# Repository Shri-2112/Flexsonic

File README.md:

# FlexSonic – Smart Glove for Gesture-to-Speech Communication
A wearable assistive device that translates hand gestures into audible speech using flex sensors, IMU, ESP32, and DFPlayer Mini.

---

## 📑 Table of Contents
- [About the Project](#-about-the-project)  
- [Tech Stack](#️-tech-stack)  
- [File Structure](#-file-structure)  
- [Getting Started](#-getting-started)  
  - [Prerequisites](#prerequisites)  
  - [Installation](#installation)  
- [Usage](#️-usage)  
- [Results and Demo](#-results-and-demo)  
- [Future Work](#-future-work)  
- [Troubleshooting](#-troubleshooting)  
- [Contributors](#-contributors)  
- [Acknowledgements and Resources](#-acknowledgements-and-resources)  
- [License](#-license)  

---

## 📖 About the Project

### Aim  
FlexSonic aims to bridge the communication gap for speech-impaired individuals by converting hand gestures into audible phrases.

### Description  
The glove uses **flex sensors** (to detect finger bending) and an **MPU6050 IMU** (to capture orientation). Sensor data is processed on an **ESP32**, which runs a simple **ML model (K-Means clustering)** to classify gestures. The recognized gesture is mapped to a **pre-recorded audio file** on a **DFPlayer Mini**, producing real-time speech output through a speaker.  

## 🛠️ Tech Stack

**Hardware:**  
- ESP32  
- Flex Sensors  
- MPU6050  
- DFPlayer Mini  
- Speaker  
- SD Card  

**Software:**  
- Arduino IDE / PlatformIO (ESP32 firmware)  
- C / Embedded C for driver code  
- Python (for ML model training & testing)
- ML Libraries: scikit-learn

**Frameworks/Tools:**  
- FreeRTOS (ESP32 task scheduling)  
- I²C, UART communication protocols  

---

## 📂 File Structure

```plaintext
Flexsonic
├── .obsidian/                  # Notes (Obsidian workspace)
│   └── Pre-requisites.md       # Basic notes
│
├── audio/                      # All audio files in use
│
├── build/                      # ESP-IDF build output
│
├── data_collection/            # Raw data logging + visualization
│   ├── data.py                 # Data logging script
│   ├── data.txt                # Raw dataset (text format)
│   ├── graph.py                # Graphical representation of dataset
 
├── data_processed/             # Processed dataset
│   ├── data_with_clusters.csv  # Clustered dataset
│   ├── gesture_labeled.csv     # Labeled dataset
│   └── gesture_parsed.csv      # Parsed dataset
│
├── main/                       # ESP32 firmware (C code)
│   ├── 1_flex.c
│   ├── 2_mpu.c
│   ├── 3_mpu_and_flex.c
│   ├── 4_sentence_gesture.c
│   └── 5_numbers_gesture.c
│
├── ml/                         # Machine Learning pipeline
│   ├── 1_raw_to_csv.py         # Convert raw logs → CSV
│   ├── 2_preprocess_train_kmeans.py  # Preprocessing + train KMeans
│   ├── 3_gesture_label.py      # Assign labels to gestures
│   ├── 4_predict_and_audio.py  # Live prediction + audio playback
│   └── kmeans_clusters.png     # Visualization of clusters
│
├── models/                     # Saved ML models
│   └── gesture_clusters.pkl
│
├── README.md                   # Project documentation
├── sdkconfig                   # ESP-IDF config file
└── CMakeLists.txt              # ESP-IDF build file

```
## 🚀 Getting Started  

### 📌 Prerequisites  
```
- **ESP-IDF v4.0+** (or Arduino IDE with ESP32 boards installed)  
- **Python 3.8+**  
```
**Required libraries (Arduino/ESP32):**  
- `esp32` board support package  
- `Adafruit_MPU6050`  
- `DFRobotDFPlayerMini`  

## ⚙️ Installation

Clone the repo:
```bash
git clone https://github.com/your_username/flexsonic.git
cd flexsonic
```
## Usage

Follow these steps to run and test the project:

1. **Connect Hardware**
   - Attach all flex sensors to the ESP32.
   - Connect the MPU6050 via I2C.
   - Insert the SD card into the DFPlayer Mini.
   - Connect a small speaker to the DFPlayer Mini output.

2. **Upload Code**
   - Open the project folder in VS Code with PlatformIO or Arduino IDE.
   - Select the ESP32 board and correct COM port.
   - Upload the firmware.

3. **Run the Project**
   - Power on the ESP32 (via USB or battery).
   - Perform different hand gestures.
   - The ESP32 will recognize gestures using sensor data.
   - DFPlayer Mini will play the corresponding pre-recorded audio.

4. **Add New Gestures**
   - Update the gesture mapping logic in `main.cpp`.
   - Add new audio files (`.mp3`) to the SD card in sequential numbering (e.g., `0001.mp3`, `0002.mp3`).
   - Re-flash the code to include new mappings.

5. **Testing**
   - Open the Serial Monitor at 115200 baud rate.
   - Debug sensor readings and check recognized gestures.
```
```
## Results & Demo

### Results
- Successfully translates predefined hand gestures into corresponding audio outputs.  
- Flex sensors + MPU6050 data are processed in real-time by the ESP32.  
- DFPlayer Mini plays pre-recorded audio files with minimal delay.  
- System can be extended by adding more gestures and audio mappings.  
- Achieved smooth serial debugging and stable performance in lab tests.  
```
```
### Demo
You can check out the project demo here:

- **Video Demo**: [Link to Demo Video]((https://drive.google.com/drive/u/1/folders/15n2ZFe-JPjL3UnUXSdUzd99bNddICzaB))  
- **Presentation Slides**: [Link to Slides]((https://www.canva.com/design/DAGyOgvHR_g/AEBH3-gOgE6V5_-GN-xAhQ/edit?ui=eyJEIjp7IlAiOnsiQiI6ZmFsc2V9fX0))  
- **Code Repository**: [GitHub Repo]((https://github.com/Shri-2112/Flexsonic/edit/main/README.md))
-  **Report**: [Report]((https://docs.google.com/document/d/1HKS84uFSLEKu0bnds3yKIxZUHhPXA11tdXNKVdhrtBQ/edit?tab=t.0)))  

```
```
## Future Work

- **Gesture Expansion**: Add more complex gesture combinations for a richer vocabulary.  
- **Dynamic Phrase Generation**: Integrate an ML model for real-time text-to-speech instead of fixed audio files.  
- **Miniaturization**: Design a compact, custom PCB to reduce size and improve portability.  
- **Wireless Connectivity**: Enable Bluetooth/Wi-Fi support for integration with smartphones or IoT devices.  
- **Energy Optimization**: Implement low-power modes for longer battery life.  
- **Multilingual Support**: Expand gesture-to-speech output across multiple languages.  
- **AI Integration**: Use advanced ML techniques (e.g., LSTM/RNN) for continuous gesture recognition.  
- **Cloud/Edge Support**: Store and update gesture mappings via a connected app or cloud server.  

## Troubleshooting

Here are some common issues and their solutions:

- **No audio output from DFPlayer Mini**  
  - Check if the SD card is properly formatted (FAT32).  
  - Ensure audio files are named correctly (e.g., `0001.mp3`, `0002.mp3`).  
  - Verify speaker connections and volume settings.  

- **ESP32 not detecting flex sensors**  
  - Recheck wiring of ADC pins.  
  - Calibrate sensor values in the code.  
  - Test with a multimeter to confirm sensor resistance changes.  

- **IMU (MPU6050) giving unstable readings**  
  - Ensure proper power supply (3.3V, not 5V).  
  - Add a small delay/filtering in code to stabilize readings.  
  - Check I2C connections (SDA, SCL).  

- **Code not compiling**  
  - Verify required libraries are installed (`DFRobotDFPlayerMini`, `Wire`, etc.).  
  - Ensure correct board and COM port are selected in Arduino IDE.  

- **Gestures not recognized correctly**  
  - Increase training data for the ML model.  
  - Adjust threshold values in the code.  
  - Check if flex sensors are securely attached to fingers.  

## Contributors

This project was made possible with the efforts of:

### Mentees
- **Janhavi Mokal**
- **Shrinivas Pathak**

### Mentors
- **Bhavesh Phundhkar**
- **Yash Suthar**
- **Swanand Patil**

Contributions are always welcome!  
Feel free to fork this repo, create a branch, and submit a pull request.  

---

## Acknowledgment

A big thank you to:  
- **SRA VJTI Mumbai** for providing the academic environment to pursue this project.  
- **Open-source communities** whose libraries and resources made implementation easier.  
- Everyone who inspired, tested, and supported FlexSonic in its early stages.  

---

## Resources

Here are some references and tools that helped during development:  

- [ESP32 Documentation](https://docs.espressif.com/projects/esp-idf/en/latest/esp32/)  
- [DFPlayer Mini](https://drive.google.com/file/d/1GSC8MQxoYqVRTvDOjcIIacYCaxSEa7fd/view) 
- [MPU6050 Guide](https://invensense.tdk.com/wp-content/uploads/2015/02/MPU-6000-Datasheet1.pdf)
- [Flex Sensors](https://cdn.sparkfun.com/assets/8/e/7/a/0/flex22.pdf)
- [EspIDF Libraries](https://docs.espressif.com/projects/esp-idf/en/stable/esp32/get-started/index.html)
- [K-means Algorithm (ML basics)](https://scikit-learn.org/stable/modules/clustering.html#k-means)

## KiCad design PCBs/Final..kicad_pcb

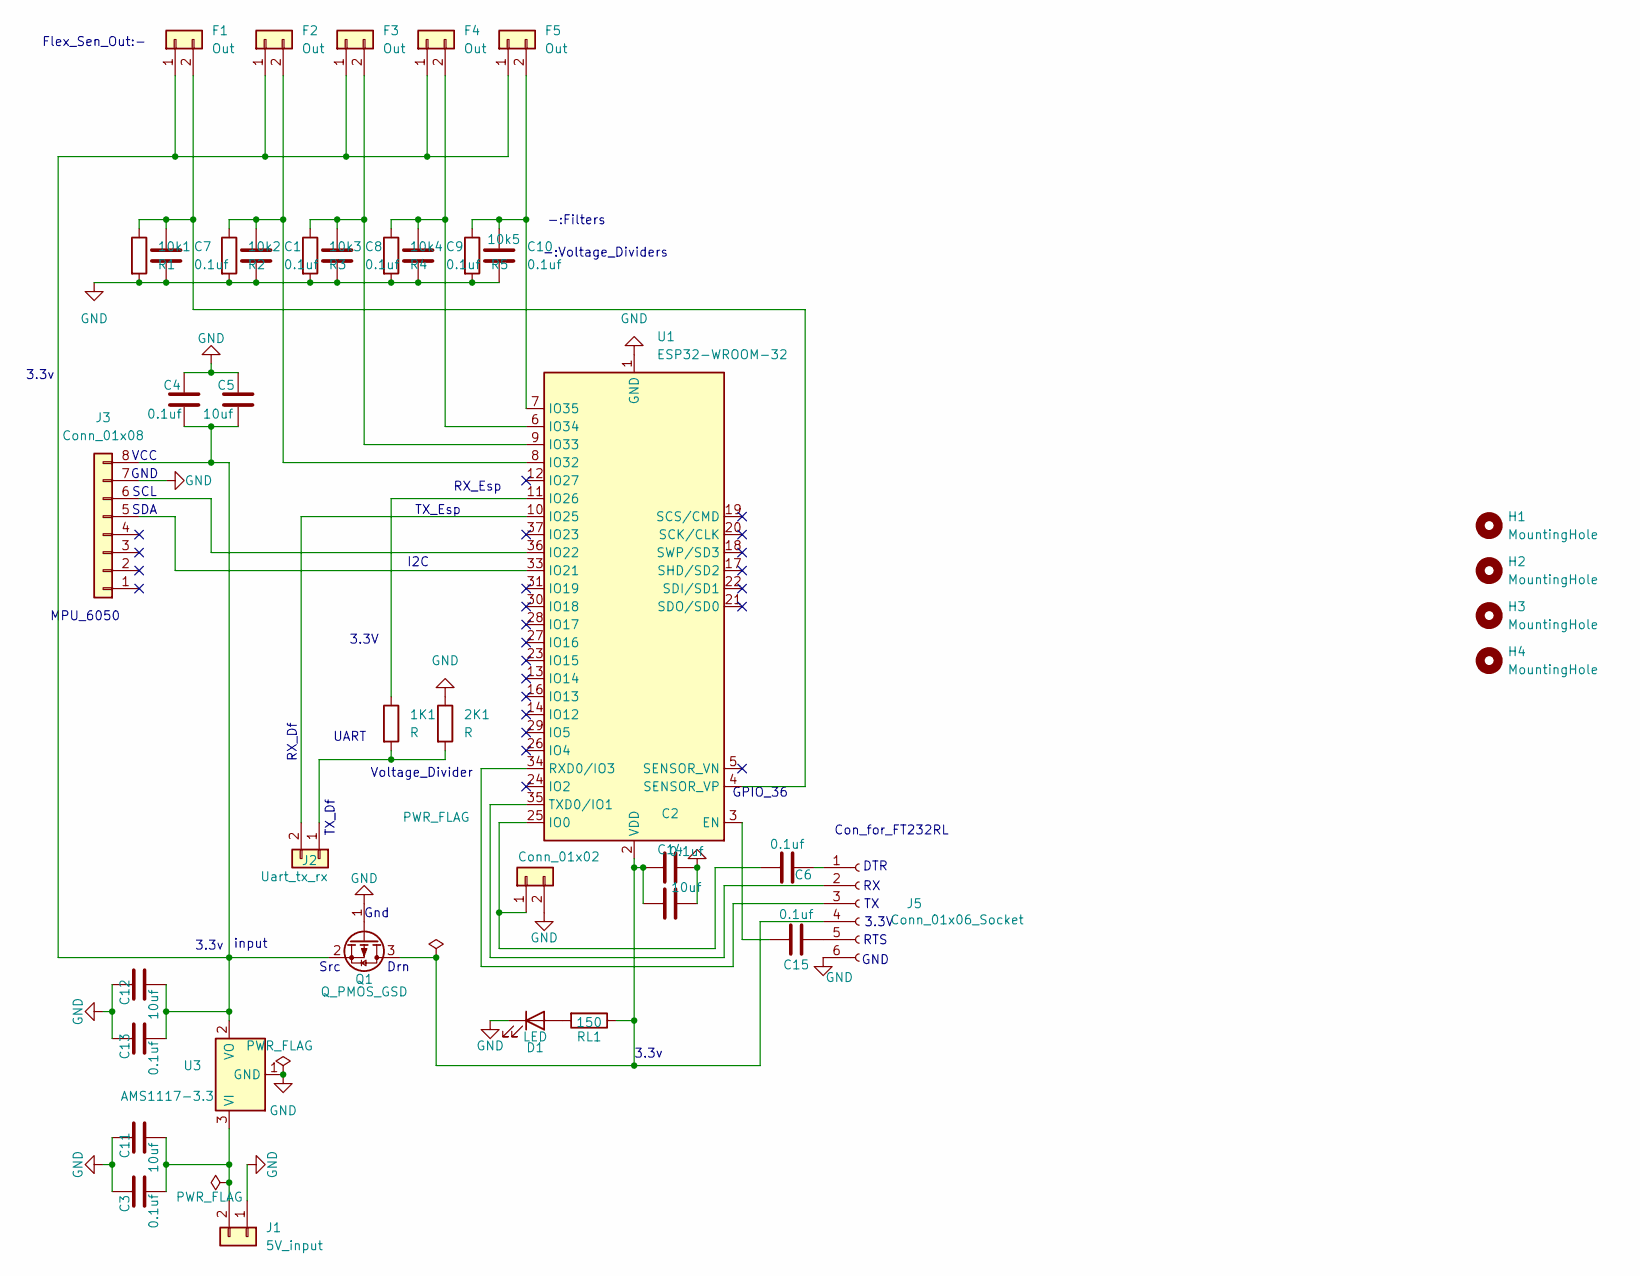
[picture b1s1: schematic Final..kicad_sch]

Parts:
1K1, 2K1: R; R_0805_2012Metric
10k1: R1; R_0805_2012Metric
10k2: R2; R_0805_2012Metric
10k3: R3; R_0805_2012Metric
10k4: R4; R_0805_2012Metric
10k5: R5; R_0805_2012Metric
C1, C2, C3, C4, C6, C7, C8, C9, C10, C13, C15: 0.1uf; C_0805_2012Metric
C5, C11, C12, C14: 10uf; C_0805_2012Metric
D1: LED; LED_0805_2012Metric
F1, F2, F3, F4, F5: Out; JST_XH_B2B-XH-A_1x02_P2.50mm_Vertical
H1: MountingHole; MountingHole_2.2mm_M2
H2, H3, H4: MountingHole; MountingHole_3.2mm_M3
J1: 5V_input; JST_XH_B2B-XH-A_1x02_P2.50mm_Vertical
J2: Uart_tx_rx; JST_XH_B2B-XH-A_1x02_P2.50mm_Vertical
J3: Conn_01x08; PinSocket_1x08_P2.54mm_Vertical
J4: Conn_01x02; JST_XH_B2B-XH-A_1x02_P2.50mm_Vertical
J5: Conn_01x06_Socket; PinSocket_1x06_P2.54mm_Horizontal
Q1: Q_PMOS_GSD; SOT-23_Handsoldering
RL1: 150; R_0805_2012Metric
U1: ESP32-WROOM-32
U3: AMS1117-3.3; SOT-223-3_TabPin2

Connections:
GND: 2K1.1, 10k1.2, 10k2.2, 10k3.2, 10k4.2, 10k5.2, C1.2, C2.2, C3.1, C4.1, C5.1, C7.1, C8.2, C9.2, C10.2, C11.1, C12.1, C13.1, C14.2, D1.1 (K), J1.1, J3.7, J4.2, J5.6, Q1.1 (G), U1.1 (GND), U1.15 (GND), U1.38 (GND), U1.39 (GND), U3.1 (GND)
unnamed: D1.2 (A), RL1.2
unnamed: C4.2, C5.2, C12.2, C13.2, F1.1, F2.1, F3.1, F4.1, F5.1, J3.8, Q1.2 (S), U3.2 (VO)
unnamed: 10k1.1, C7.2, F1.2, U1.4 (SENSOR_VP)
unnamed: 10k2.1, C1.1, F2.2, U1.8 (IO32)
unnamed: 10k3.1, C8.1, F3.2, U1.9 (IO33)
unnamed: 10k4.1, C9.1, F4.2, U1.6 (IO34)
unnamed: 10k5.1, C10.1, F5.2, U1.7 (IO35)
unnamed: C3.2, C11.2, J1.2, U3.3 (VI)
unnamed: 1K1.2, 2K1.2, J2.1
unnamed: J2.2, U1.10 (IO25)
unnamed: J3.5, U1.33 (IO21)
unnamed: J3.6, U1.36 (IO22)
unnamed: C6.1, J4.1, U1.25 (IO0)
unnamed: C6.2, J5.1
unnamed: J5.2, U1.35 (TXD0/IO1)
unnamed: J5.3, U1.34 (RXD0/IO3)
unnamed: C2.1, C14.1, J5.4, Q1.3 (D), RL1.1, U1.2 (VDD)
unnamed: C15.2, J5.5
unnamed: C15.1, U1.3 (EN)
unnamed: 1K1.1, U1.11 (IO26)

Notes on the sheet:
I2C
GND
RX_Df
SDA
TX_Df
Voltage_Divider
3.3v
-:Filters
input
Gnd
RTS
TX_Esp
-:Voltage_Dividers
Src
3.3V
MPU_6050
DTR
RX_Esp
GPIO_36
Flex_Sen_Out:-
3.3V
SCL
UART
VCC
Con_for_FT232RL
Drn

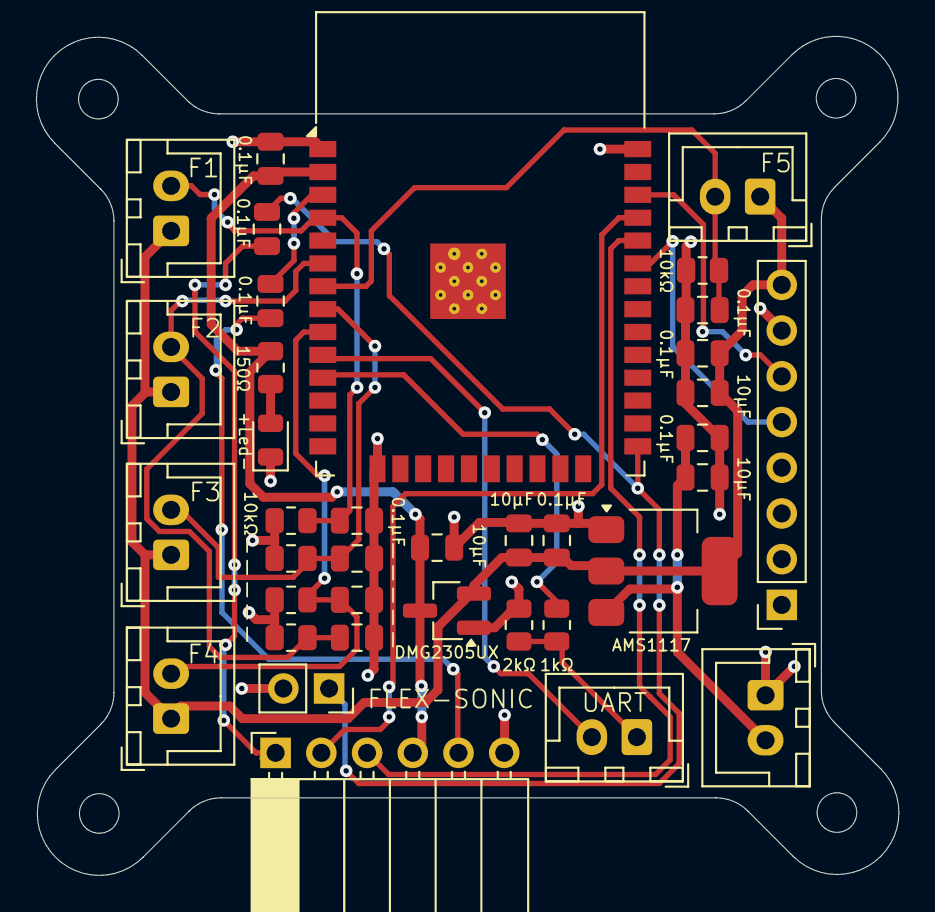
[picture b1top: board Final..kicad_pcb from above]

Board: 2 copper layers, 47.9 x 46.6 mm, 37 parts (0 on the bottom side), 21 nets.

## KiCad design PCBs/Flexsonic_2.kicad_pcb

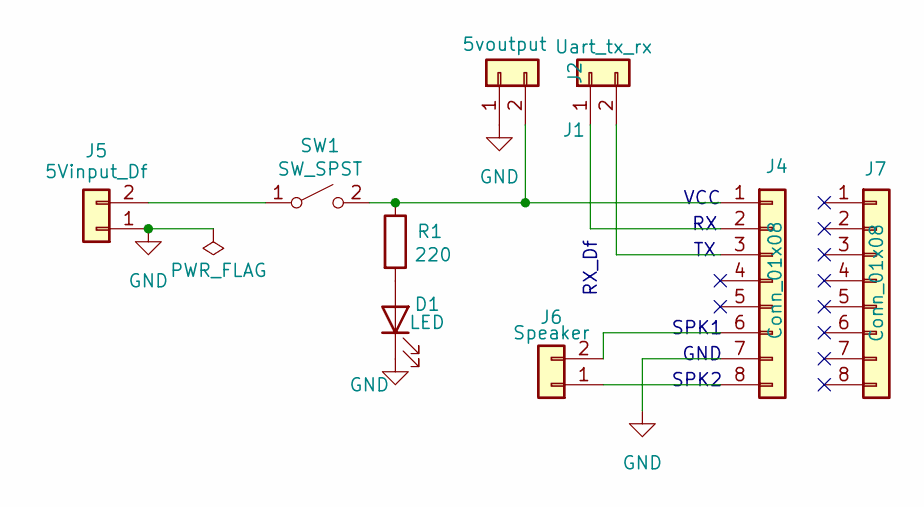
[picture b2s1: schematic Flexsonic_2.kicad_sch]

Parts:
D1: LED; LED_0805_2012Metric
J1: Uart_tx_rx; JST_PH_B2B-PH-K_1x02_P2.00mm_Vertical
J2: 5voutput; JST_PH_B2B-PH-K_1x02_P2.00mm_Vertical
J4, J7: Conn_01x08; PinHeader_1x08_P2.54mm_Vertical
J5: 5Vinput_Df; JST_PH_B2B-PH-K_1x02_P2.00mm_Vertical
J6: Speaker; JST_PH_B2B-PH-K_1x02_P2.00mm_Vertical
R1: 220; R_0805_2012Metric
SW1: SW_SPST; SW_SPST_PTS645Sx43SMTR92

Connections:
GND: D1.1 (K), J2.1, J4.7, J5.1
unnamed: D1.2 (A), R1.2
unnamed: J1.1, J4.2
unnamed: J1.2, J4.3
unnamed: J2.2, J4.1, R1.1, SW1.2 (B)
unnamed: J4.6, J6.2
unnamed: J4.8, J6.1
unnamed: J5.2, SW1.1 (A)

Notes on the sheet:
SPK1
GND
SPK2
VCC
RX_Df

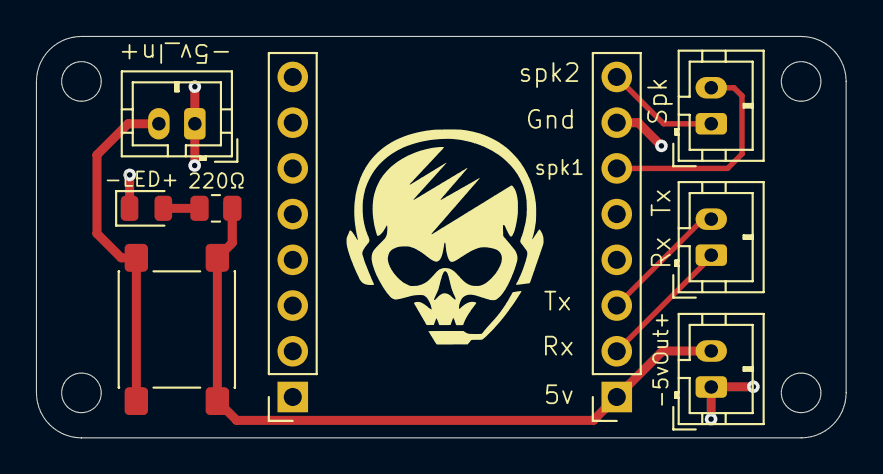
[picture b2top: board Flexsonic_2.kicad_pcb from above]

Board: 2 copper layers, 45.0 x 22.3 mm, 9 parts (0 on the bottom side), 8 nets.

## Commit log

2025-06-27 Added Obsidian notes
2025-07-09 Add C_practice files to Shriniwas branch
2025-07-25 Create Pre-requisites
2025-07-25 Rename Pre-requisites to Pre-requisites.md
2025-07-25 Initial commit to Janhavi Branch
2025-08-12 Create Machine Learning
2025-09-06 Rename flex.c to 1_flex.c
2025-09-06 Rename mpu_and_flex.c to 3_mpu_and_flex.c
2025-09-06 Rename mpu.c to 2_mpu.c
2025-09-06 Create audio
2025-09-07 Added PCBs and Schematics folders
2025-09-07 Uploaded All Files
